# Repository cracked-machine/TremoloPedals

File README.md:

# TremoloPedals

[Atomizer Tremolo](atomizer/atomizer.md)

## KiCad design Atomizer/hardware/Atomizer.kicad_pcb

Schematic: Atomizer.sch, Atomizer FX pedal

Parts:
C1: 1uF; C_0805_2012Metric_Pad1.15x1.40mm_HandSolder
CP_INV1, CP_INV2: 10uF; CP_Elec_4x5.4; MouserNo 140-VE100M1CTR0405
C_BP3, C_BP4, C_BP5: 100nF; C_0805_2012Metric_Pad1.15x1.40mm_HandSolder; MouserNo 710-885012207098
J_IN1: JACK__MONO_2P_NC; 6_35MM_JACK_MONO_FlatTop_notab; MouserNo 550-10284G
J_OUT1: JACK__MONO_2P_NC; 6_35MM_JACK_MONO_FlatTop_notab; MouserNo 550-10284G
J_PWR1: Jack-DC; BarrelJack_Horizontal; MouserNo 502-RAPC722X
P_DEPTH1: B50k; Potentiometer_Alps_RK09L_Single_Vertical; MouserNo 688-RK09L1140A5P
P_VOL1: B10K; Potentiometer_Alps_RK09L_Single_Vertical; MouserNo 688-RK09L1140A66
R1, R3: 1K; R_0805_2012Metric_Pad1.15x1.40mm_HandSolder; MouserNo 279-CRGP0805F1K0
R2: 330R; R_0805_2012Metric_Pad1.15x1.40mm_HandSolder; MouserNo 71-CRCW0805330RFKEAC
R4: 270R; R_0805_2012Metric_Pad1.15x1.40mm_HandSolder; MouserNo 667-ERJ-6ENF2700V
R5: 47R; R_0805_2012Metric_Pad1.15x1.40mm_HandSolder; MouserNo 667-ERJ-6ENF47R0V
R6: 100K; R_0805_2012Metric_Pad1.15x1.40mm_HandSolder
R_GAIN1: 2K7; R_0805_2012Metric_Pad1.15x1.40mm_HandSolder; MouserNo 279-CRGCQ0805F2K7
R_PD1: 1M; R_0805_2012Metric_Pad1.15x1.40mm_HandSolder; MouserNo 755-UCR10EVHFSR022
U_BUF1: TL072; SOIC-8_3.9x4.9mm_P1.27mm; MouserNo 621-TL072SG-13
U_INV1: TC7662Bx0A; SOIC-8_3.9x4.9mm_P1.27mm; MouserNo 579-TC7660SEOA713
U_NREG1: LM337_SOT223; SOT-223-3_TabPin2; MouserNo 926-LM337IMP/NOPB
U_PREG1: LM317_3PinPackage; SOT-223-3_TabPin2; MouserNo 595-LM317DCYR

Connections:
+5V: C_BP3.2, R2.1, U_BUF1.8 (V+), U_PREG1.2; also elsewhere on the board
+9V: C_BP5.2, J_PWR1.2, U_INV1.1, U_INV1.8, U_PREG1.3
-5V: C_BP4.1, R4.2, U_BUF1.4 (V-), U_NREG1.3
-9V: CP_INV2.2, U_INV1.5, U_NREG1.2
/3PDT_2_EXT: J_IN1.1; also elsewhere on the board
/3PDT_3_EXT: R_PD1.1, U_BUF1.3 (+); also elsewhere on the board
/3PDT_5_EXT: J_OUT1.1; also elsewhere on the board
/3PDT_6_EXT: C1.1, R6.1; also elsewhere on the board
/Atomizer_Clock/CLK_OUT: P_DEPTH1.3; also elsewhere on the board
/GND: CP_INV2.1, C_BP3.1, C_BP4.2, C_BP5.1, J_IN1.2, J_IN1.3, J_IN1.4, J_OUT1.2, J_OUT1.3, J_OUT1.4, J_PWR1.1, R1.2, R3.2, R6.2, R_GAIN1.2, R_PD1.2, U_INV1.3, U_INV1.6; also elsewhere on the board
unnamed: C1.2, P_VOL1.3, U_BUF1.7
unnamed: CP_INV1.1, U_INV1.2
unnamed: CP_INV1.2, U_INV1.4
unnamed: P_DEPTH1.1, U_BUF1.1, U_BUF1.2 (-)
unnamed: P_DEPTH1.2, U_BUF1.5 (+)
unnamed: P_VOL1.1, P_VOL1.2, R_GAIN1.1, U_BUF1.6 (-)
unnamed: R1.1, R2.2, U_PREG1.1
unnamed: R3.1, R5.2, U_NREG1.1
unnamed: R4.1, R5.1

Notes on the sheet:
POWER SUPPLY
FOOTSWITCH
LFO
Guitar Fx pedals are Centre-Negative

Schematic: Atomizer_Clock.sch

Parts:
CP_FAST1: 22uF; CP_Elec_4x5.4; Tolerance 20%; Voltage Rating DC 10 DC; MouserNo 710-875105240003
CP_SLOW1: 220uF; CP_Elec_6.3x5.4; Voltage Rating DC 16 VDC; Tolerance 20 %; MouserNo 667-EEE-FPC221XAP
C_BP1: 100nF; C_0805_2012Metric_Pad1.15x1.40mm_HandSolder; MouserNo 710-885012207098
C_BP2: 10uF; C_0805_2012Metric_Pad1.15x1.40mm_HandSolder; MouserNo 81-GRM21BC81C106KE5K
D_HI1, D_HI2, D_HI3: 1N914_VF1; D_SOD-123; MouserNo 821-1N914BWRH
D_LED1: LED; LED_D5.0mm; MouserNo 859-LTL-307EE
D_LEDHI1: LED; LED_D3.0mm; MouserNo 941-C4SMABGFCR2T3451
D_LEDLO1: LED; LED_D3.0mm; MouserNo 941-C4SMABGFCR2T3451
D_LO1, D_LO2, D_LO3: 1N914_VF1; D_SOD-123; MouserNo 821-1N914BWRH
J_ICSP1: Conn_02x03_Odd_Even; PinHeader_2x03_P2.54mm_Vertical; MouserNo 538-22-28-4062
P_OSCOFF1: B10K; Potentiometer_Alps_RK09L_Single_Vertical; MouserNo 688-RK09L1140A66
P_OSCON1: B10K; Potentiometer_Alps_RK09L_Single_Vertical; MouserNo 688-RK09L1140A66
R_LPF1: 1K; R_0805_2012Metric_Pad1.15x1.40mm_HandSolder; MouserNo 279-CRGP0805F1K0
R_MLED1: 22K; R_0805_2012Metric_Pad1.15x1.40mm_HandSolder; MouserNo 667-ERJ-6ENF2202V
R_MODE1: 1K; R_0805_2012Metric_Pad1.15x1.40mm_HandSolder; MouserNo 279-CRGP0805F1K0
R_OSCOFF1: 1K; R_0805_2012Metric_Pad1.15x1.40mm_HandSolder; MouserNo 279-CRGP0805F1K0
R_OSCON1: 1K; R_0805_2012Metric_Pad1.15x1.40mm_HandSolder; MouserNo 279-CRGP0805F1K0
SW_ATTACK1: SW_SPDT; Dailywell_SPDT; MouserNo 108-2MS1T1B1M2QE-EVX
SW_MODE1: 1-1825910-4; SW_2-1825910-7; MouserNo 506-1-1825910-4
U_CLK1: ATtiny85-20SU; SOIJ-8_5.3x5.3mm_P1.27mm; MouserNo 556-ATTINY85-20SU
U_OPTO1: ACPL-217; SO-4_4.4x2.3mm_P1.27mm; MouserNo 630-ACPL-217-50BE

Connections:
/3PDT_8_EXT: C_BP1.1, C_BP2.1, D_LO3.2, J_ICSP1.2, R_OSCOFF1.2, R_OSCON1.2, U_CLK1.8 (VCC); also elsewhere on the board
/Atomizer_Clock/CLK_OUT: U_OPTO1.4; also elsewhere on the board
/Atomizer_Clock/CLK_OUT_PIN: J_ICSP1.1, R_LPF1.2, U_CLK1.6 (PB1)
/Atomizer_Clock/FREQ_ADJ_OFF_PIN: P_OSCOFF1.2, U_CLK1.3 (XTAL2/PB4)
/Atomizer_Clock/FREQ_ADJ_ON_PIN: P_OSCON1.2, U_CLK1.2 (XTAL1/PB3)
/Atomizer_Clock/MODE_BTN_PIN: J_ICSP1.4, R_MODE1.1, U_CLK1.5 (AREF/PB0)
/Atomizer_Clock/MODE_LED_PIN: J_ICSP1.3, R_MLED1.2, U_CLK1.7 (PB2)
/Atomizer_Clock/RESET: J_ICSP1.5, U_CLK1.1 (~RESET~/PB5)
/GND: CP_FAST1.2, CP_SLOW1.2, C_BP1.2, C_BP2.2, D_HI3.1, J_ICSP1.6, P_OSCOFF1.1, P_OSCON1.1, SW_MODE1.3, U_CLK1.4 (GND), U_OPTO1.2, U_OPTO1.3; also elsewhere on the board
unnamed: CP_FAST1.1, SW_ATTACK1.1
unnamed: CP_SLOW1.1, SW_ATTACK1.3
unnamed: D_HI1.1, D_HI2.2
unnamed: D_HI1.2, D_LEDHI1.1
unnamed: D_HI2.1, D_HI3.2
unnamed: D_LED1.1, SW_ATTACK1.2, U_OPTO1.1
unnamed: D_LED1.2, R_LPF1.1
unnamed: D_LEDHI1.2, D_LEDLO1.1, R_MLED1.1
unnamed: D_LEDLO1.2, D_LO1.1
unnamed: D_LO1.2, D_LO2.1
unnamed: D_LO2.2, D_LO3.1
unnamed: P_OSCOFF1.3, R_OSCOFF1.1
unnamed: P_OSCON1.3, R_OSCON1.1
unnamed: R_MODE1.2, SW_MODE1.2

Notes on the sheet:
Diodes prevent switch on when MODE_LED_PIN is in Tri-State
MOSI
VCC
GND
SCK
MISO
RESET

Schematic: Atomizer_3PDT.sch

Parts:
J_AUXTOMAIN1: Conn_02x05_Counter_Clockwise; IDCHeader_02x05_P2.54mm_Vertical_Counter_Clockwise; MouserNo 538-22-28-4102
J_MAINTOAUX1: Conn_02x05_Counter_Clockwise; IDCHeader_02x05_P2.54mm_Vertical_Clockwise; MouserNo 538-22-28-4102
SW_EN1: SW_3PDT_on_on; SW_3PDT_W18MM_L17.3MM_P5.3MM_D2MM; MouserNo 612-FS573PLT2B2M2QE

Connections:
+5V: J_MAINTOAUX1.9; also elsewhere on the board
/3PDT_2_EXT: J_MAINTOAUX1.2; also elsewhere on the board
/3PDT_3_EXT: J_MAINTOAUX1.3; also elsewhere on the board
/3PDT_4_EXT: J_MAINTOAUX1.1, J_MAINTOAUX1.4
/3PDT_5_EXT: J_MAINTOAUX1.5; also elsewhere on the board
/3PDT_6_EXT: J_MAINTOAUX1.6; also elsewhere on the board
/3PDT_8_EXT: J_MAINTOAUX1.8; also elsewhere on the board
/Atomizer_3PDT/3PDT_1_INT: J_AUXTOMAIN1.1, SW_EN1.1
/Atomizer_3PDT/3PDT_2_INT: J_AUXTOMAIN1.2, SW_EN1.2
/Atomizer_3PDT/3PDT_3_INT: J_AUXTOMAIN1.3, SW_EN1.3
/Atomizer_3PDT/3PDT_4_INT: J_AUXTOMAIN1.4, SW_EN1.4
/Atomizer_3PDT/3PDT_5_INT: J_AUXTOMAIN1.5, SW_EN1.5
/Atomizer_3PDT/3PDT_6_INT: J_AUXTOMAIN1.6, SW_EN1.6
/Atomizer_3PDT/3PDT_7_INT: J_AUXTOMAIN1.7, SW_EN1.7
/Atomizer_3PDT/3PDT_8_INT: J_AUXTOMAIN1.8, SW_EN1.8
/Atomizer_3PDT/3PDT_9_INT: J_AUXTOMAIN1.9, SW_EN1.9

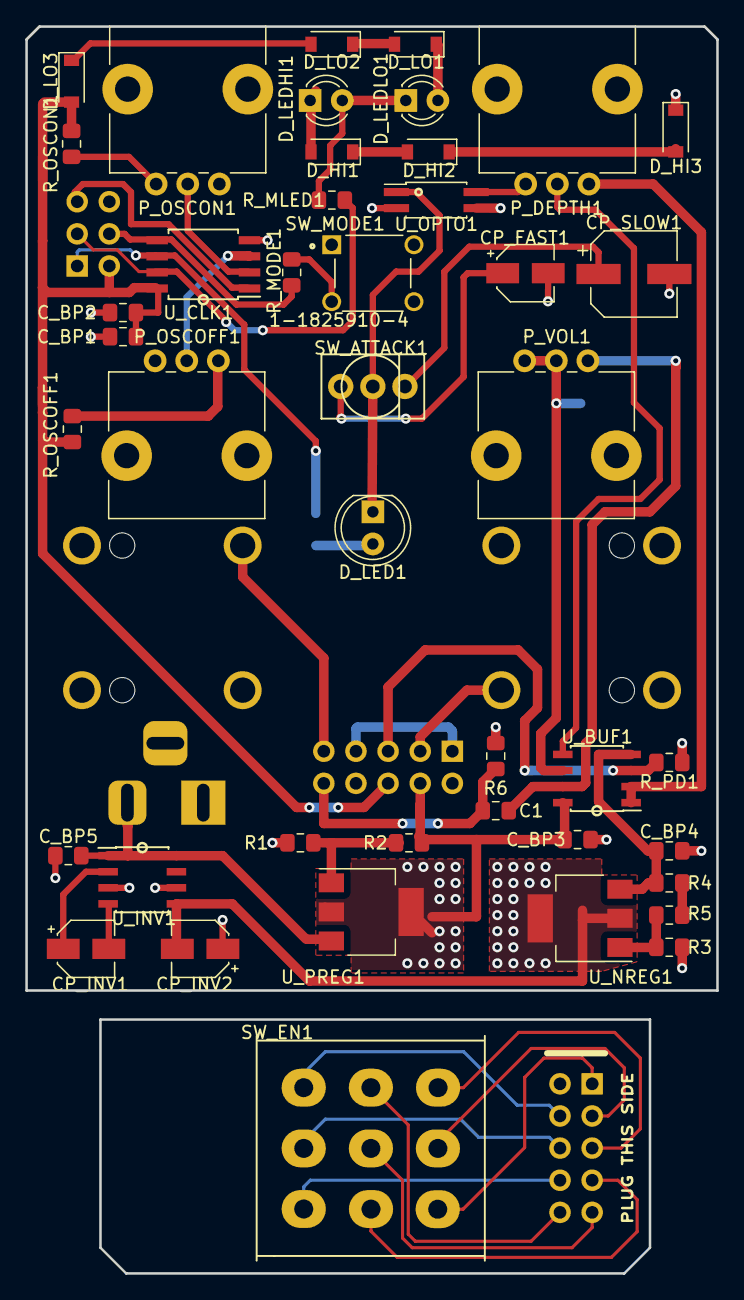
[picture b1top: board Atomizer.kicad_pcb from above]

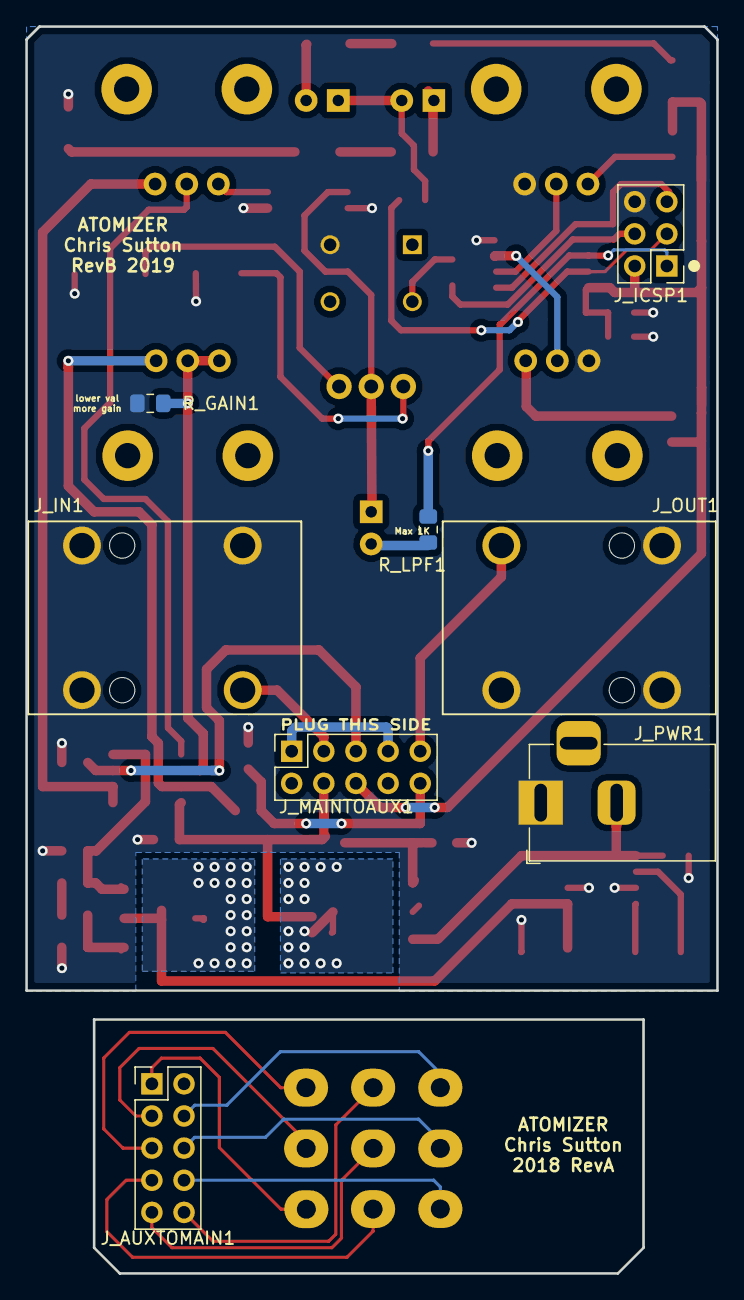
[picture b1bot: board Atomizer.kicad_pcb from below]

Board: 2 copper layers, 54.6 x 98.6 mm, 51 parts (8 on the bottom side), 50 nets.

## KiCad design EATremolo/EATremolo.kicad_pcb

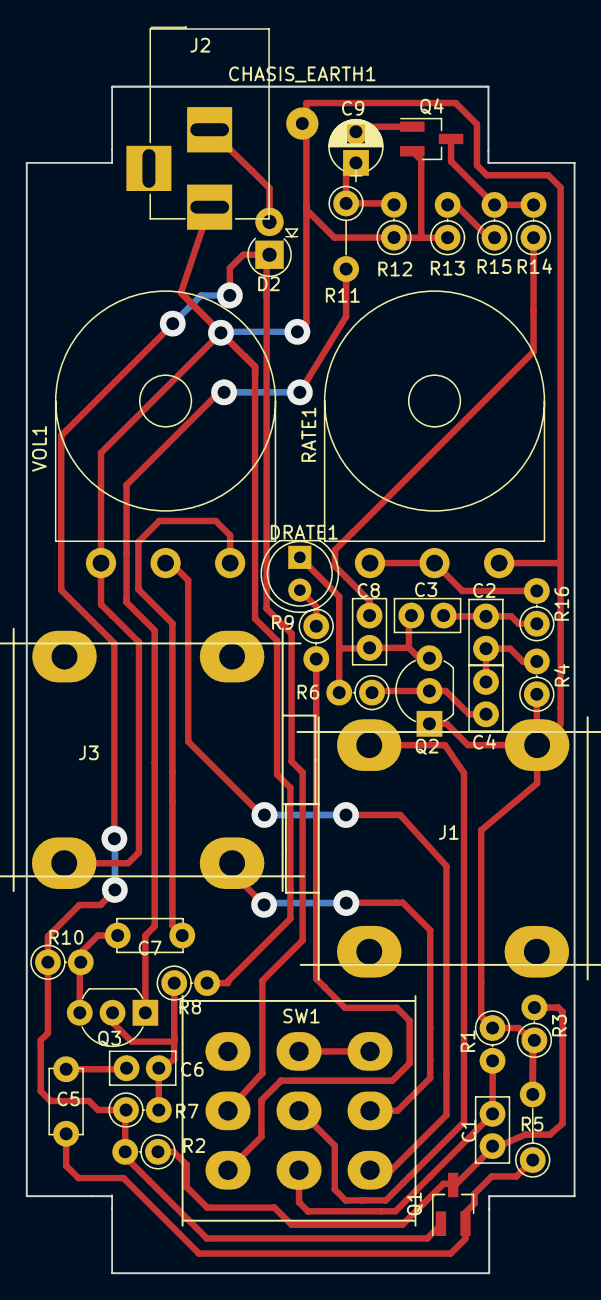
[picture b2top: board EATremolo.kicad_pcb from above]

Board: 2 copper layers, 42.4 x 96.5 mm, 38 parts (0 on the bottom side), 27 nets.

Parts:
C1: 47nF; C_Disc_2mmPads
C2, C3, C4: 1uF; C_Disc_2mmPads
C5: 10uF; C_Disc_P5.0mm_2mmPads
C6: 220nF; C_Disc_2mmPads
C7: 470nF; C_Disc_P5.0mm_2mmPads
C8: 470nF; C_Disc_2mmPads
C9: 10uF; CP_Radial_D4_P2_PadSize2_Drill1
CHASIS_EARTH1: CONN_01X01; SolderWirePad_single_1mmDrill
D2: D_Schottky; D_DO-41_SOD81_P2.54mm_Vertical_AnodeUp
DRATE1: LED; LED_D5.0mm
J1, J3: JACK__MONO_2P_NC; JackSocket_Mono_PCB
J2: BARREL_JACK
Q1, Q4: Q_NJFET_DSG; SOT-23_Handsoldering
Q2, Q3: Q_NPN_EBC; TO-92_Inline_Wide
R1, R2, R3: 1M; R_Axial_DIN0207_Vertical_2mmPad
R4: 15K; R_Axial_DIN0207_Vertical_2mmPad
R5: 10K; R_Axial_DIN0207_P5.08mm_2mmPads
R6: 2.2M; R_Axial_DIN0207_Vertical_2mmPad
R7: 560K; R_Axial_DIN0207_Vertical_2mmPad
R8: 150K; R_Axial_DIN0207_Vertical_2mmPad
R9: 10K; R_Axial_DIN0207_Vertical_2mmPad
R10: 4.7K; R_Axial_DIN0207_Vertical_2mmPad
R11: 180R; R_Axial_DIN0207_P5.08mm_2mmPads
R12: 1.2K; R_Axial_DIN0207_Vertical_2mmPad
R13: 68k; R_Axial_DIN0207_Vertical_2mmPad
R14: 180K; R_Axial_DIN0207_Vertical_2mmPad
R15: 100K; R_Axial_DIN0207_Vertical_2mmPad
R16: 1K; R_Axial_DIN0207_Vertical_2mmPad
RATE1: B100K; Potentiometer_Omeg_PC16PU_Horizontal
SW1: SW_3PDT_on_on; SW_3PDT_W18MM_L17.3MM_P5.3MM_D2MM
VOL1: A25K; Potentiometer_Omeg_PC16PU_Horizontal

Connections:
/+9V: D2.1, Q1.1, R2.2, R7.1, R10.1, SW1.2
/GND: CHASIS_EARTH1.1, J1.4, J2.1, J3.4, Q2.1, Q4.2, R1.1, R3.1, R4.1, R5.2, R8.2, R12.1, R13.1, RATE1.1, VOL1.3
unnamed: C1.1, Q1.3, R2.1, R3.2
unnamed: C1.2, R1.2, SW1.6
unnamed: C2.1, C3.2, R16.1
unnamed: C2.2, C4.1, R4.2
unnamed: C3.1, C8.2, DRATE1.1, Q2.3, R6.2
unnamed: C4.2, Q2.2, R6.1
unnamed: C5.1, Q1.2, R5.1
unnamed: C5.2, C6.2
unnamed: C6.1, Q3.2, R7.2, R8.1
unnamed: C7.1, VOL1.1
unnamed: C7.2, Q3.3, R10.2
unnamed: C8.1, R14.1
unnamed: C9.1, R11.1, R12.2
unnamed: C9.2, Q4.1
unnamed: D2.2, J2.2
unnamed: DRATE1.2, R9.1
unnamed: J1.1, SW1.5
unnamed: J3.1, SW1.8
unnamed: Q3.1, R11.2
unnamed: Q4.3, R14.2, R15.2
unnamed: R9.2, SW1.3
unnamed: R13.2, R15.1
unnamed: R16.2, RATE1.2, RATE1.3
unnamed: SW1.4, SW1.7
unnamed: SW1.9, VOL1.2

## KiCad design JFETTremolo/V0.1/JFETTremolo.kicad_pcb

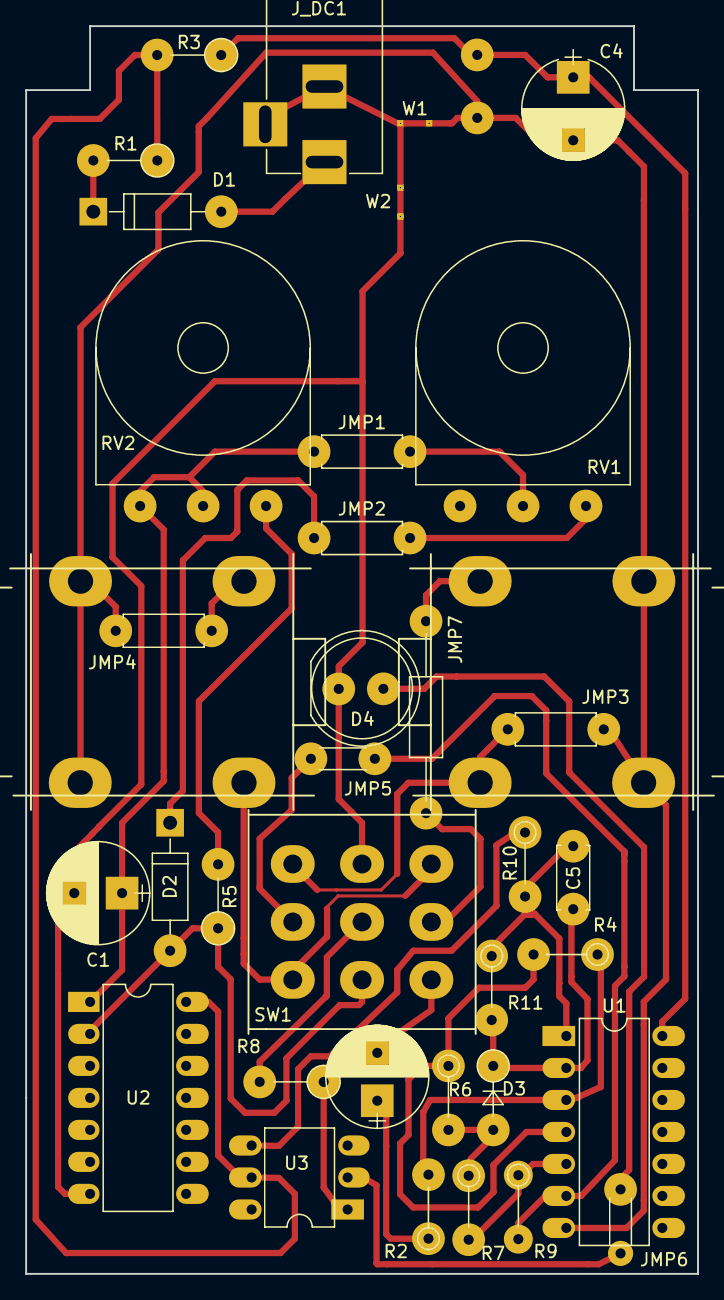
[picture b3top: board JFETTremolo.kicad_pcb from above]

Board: 2 copper layers, 53.3 x 99.1 mm, 38 parts (1 on the bottom side), 31 nets.

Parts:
C1: 10U; CP_Radial_D8.0mm_P3.80mm
C2: 1u; CP_Radial_D8.0mm_P3.80mm
C3: 10n; C_Disc_D5.0mm_W2.5mm_P5.00mm
C4: 47u; CP_Radial_D8.0mm_P5.00mm
C5: 470n; C_Disc_D5.0mm_W2.5mm_P5.00mm
D1, D2: D; D_DO-41_SOD81_P10.16mm_Horizontal
D3: D; D_DO-35_SOD27_P5.08mm_Vertical_AnodeUp
D4: LED; LED_D8.0mm
JMP1, JMP2, JMP3, JMP4: 0; R_Axial_DIN0207_L6.3mm_D2.5mm_P7.62mm_Horizontal
JMP5, JMP6: 0; R_Axial_DIN0204_L3.6mm_D1.6mm_P5.08mm_Horizontal
JMP7: 0; R_Axial_DIN0207_L6.3mm_D2.5mm_P15.24mm_Horizontal
J_DC1: BARREL_JACK
J_IN1: JACK__MONO_2P_NC; JackSocket_Mono_PCB
J_OUT1: JACK__MONO_2P_NC; JackSocket_Mono_PCB
R1: 100R; R_Axial_DIN0207_L6.3mm_D2.5mm_P5.08mm_Vertical
R2, R4, R6, R7, R9, R10, R11: 100K; R_Axial_DIN0204_L3.6mm_D1.6mm_P5.08mm_Vertical
R3, R5: 10K; R_Axial_DIN0207_L6.3mm_D2.5mm_P5.08mm_Vertical
R8: 100K; R_Axial_DIN0207_L6.3mm_D2.5mm_P5.08mm_Vertical
RV1, RV2: 100K; Potentiometer_Omeg_PC16PU_Horizontal
SW1: SW_3PDT_on_on; SW_3PDT_W18MM_L17.3MM_P5.3MM_D2MM
U1: CD4069; DIP-14_W7.62mm
U2: 4584; DIP-14_W7.62mm
U3: 4N25; DIP-6_W7.62mm
W1, W2: NetTie

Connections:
/clk_gnd: C1.2, D4.1, SW1.6, U2.7, W2.2
/clk_ota: D2.2, R5.1, SW1.4, U2.2
/clk_vdd: R1.1, R3.2, U2.14, U3.5
/fxin: C2.2, SW1.1
/fxout: JMP5.1, JMP5.2, R9.2, SW1.8, U1.6
/gnd: J_DC1.2, J_DC1.3, W1.1, W2.1
/mclk: C5.1, D3.1, R11.2, U1.2
/ota_clk: R10.1, U3.4
/sig_gnd: C3.2, C4.2, JMP3.1, JMP3.2, JMP4.2, J_IN1.2, J_IN1.3, J_IN1.4, J_OUT1.3, J_OUT1.4, SW1.9, U1.7, W1.2
/sig_out: J_OUT1.1, SW1.3, SW1.7
/sig_vdd: C3.1, C4.1, R3.1, U1.14
/sigin: JMP7.2, J_IN1.1
unnamed: C1.1, JMP1.1, RV2.2, RV2.3, U2.1
unnamed: C2.1, R2.1
unnamed: C5.2, R10.2, R11.1, U1.1
unnamed: D1.1, R1.2
unnamed: D1.2, J_DC1.1
unnamed: D2.1, JMP2.1
unnamed: D3.2, R6.2, R7.1
unnamed: D4.2, JMP6.2
unnamed: JMP1.2, RV1.2
unnamed: JMP2.2, RV1.1
unnamed: JMP4.1, J_OUT1.2
unnamed: JMP6.1, U3.2
unnamed: JMP7.1, SW1.2
unnamed: R2.2, R4.1, U1.3
unnamed: R4.2, R6.1, U1.4
unnamed: R5.2, RV2.1
unnamed: R7.2, R9.1, U1.5
unnamed: R8.1, U3.1
unnamed: R8.2, SW1.5

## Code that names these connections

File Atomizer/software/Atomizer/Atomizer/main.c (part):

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volatile unsigned int lowerpot = 0;		// the bottom potentiometer

#define _ADCLA 0x20	// ADC Left Adjust Result
#define _ADC0EN 0x00	// PB5 - MUX(3:0) = 0000; Use bitwise AND to set ADC0 ( e.g. ADMUX &= ADC0EN; )
#define _ADC1EN 0x01	// PB2 - MUX(3:0) = 0001; Use bitwise OR to set ADC1 ( e.g. ADMUX |= ADC1EN; )
#define _ADC2EN 0x02	// PB4 - MUX(3:0) = 0010; Use bitwise OR to set ADC2 ( e.g. ADMUX |= ADC2EN; )
#define _ADC3EN 0x03	// PB3 - MUX(3:0) = 0011; Use bitwise OR to set ADC3 ( e.g. ADMUX |= ADC3EN; )

// PCINT variables
// NORMAL	=	Synchronized-duty Tremolo (lowerpot does nothing)
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	/////	PIN USAGE
	///////////////////////
	///
	//		PB0 - INPUT  - Mode Button
	//		PB1 - OUTPUT - Tremolo Clock 
	//		PB2 - OUTPUT - Mode LEDs
	//		PB3 - INPUT  - Hi Adjust Pot
	//		PB4 - INPUT  - Lo Adjust Pot
	///
	////////////////////////
	
	
	
	// clock signal (output)
	PORTB |= (1<<PB1);
	DDRB |= (1<<DDB1);
	
	// ADC3+4 (input)
	PORTB &= ~(1<<PB3);
	DDRB &= ~(1<<DDB3);
	PORTB &= ~(1<<PB4);
	DDRB &= ~(1<<DDB4);
		
	///////////////////////////////////
	//// PCINT setup
	///////////////////////////////////
	
	// set PB0 to input
	DDRB &= ~(1<<DDB0);
	// set PB0 pull-up
	PORTB |= 1<<PB0;
	
	// enable PC Interrupts
	GIMSK |= (1<<PCIE);
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	///////////////////////////////////

	
	// VCC used as Voltage Reference, disconnected from PB0 (AREF).
	ADMUX &= ~((1<<REFS0) | (1<<REFS1));
	
	// ADC Right Adjust Result
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		case NORMAL:
			// Tri-State mode LED pin (LEDS off)
			DDRB &= ~(1<<DDB2);
			PORTB &= ~(1<<PB2);
			break;
			
		case SKEW:
			// Logic one to mode LED pin 
			DDRB |= (1<<DDB2);
			PORTB |= (1<<PB2);
			break;
		
		case SWEEP:
			// Logic zero to mode LED pin 
			DDRB |= (1<<DDB2);
			PORTB &= ~(1<<PB2);
			break;
		/* abandoned *see top*
		case FADE:
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	{
		case NORMAL:
			
			// disable Timer0 output to OC0B (PB1)
			TCCR0A = 0;
			
			///////////////////////////////////
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			// Timer/Counter1 is reset to $00 after a compare match with OCR1C register value 
			TCCR1 |= (1<<CTC1);
	
			// enable toggle output on OC1A (PB1) output line.
			TCCR1 |= (0<<COM1A1) | (1<<COM1A0);
			
			// Timer/Counter1 Prescale Select PCK/2048
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			
		case SKEW:
			
			// disable Timer1 output to OC1A (PB1)
			TCCR1 = 0;
			
			///////////////////////////////////
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			
			//Normal port operation, OC0A disconnected
			TCCR0A |= (0<<COM0A1) | (0<<COM0A0);
			// Enable OC0B (PB1) output. (Clear OC0B on Compare Match, set OC0B at BOTTOM - non-inverting mode)
			TCCR0A |= (1<<COM0B1) | (0<<COM0B0);
			// Mode 5: phase PWM
			TCCR0A |= (0<<WGM01) | (1<<WGM00);
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		
		case SWEEP:
		
			// disable Timer0 output to OC0B (PB1)
			TCCR0A = 0;
			
			///////////////////////////////////
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			// Timer/Counter1 is reset to $00 after a compare match with OCR1C register value
			TCCR1 |= (1<<CTC1);
			
			// enable toggle output on OC1A (PB1) output line.
			TCCR1 |= (0<<COM1A1) | (1<<COM1A0);
			
			// Timer/Counter1 Prescale Select PCK/2048
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			/*  abandoned *see top*
			case FADE:
			
			// disable Timer1 output to OC1A (PB1)
			TCCR1 = 0;
			
			///////////////////////////////////
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			
			//Normal port operation, OC0A disconnected
			TCCR0A |= (0<<COM0A1) | (0<<COM0A0);
			// Enable OC0B (PB1) output. (Clear OC0B on Compare Match, set OC0B at BOTTOM - non-inverting mode)
			TCCR0A |= (1<<COM0B1) | (0<<COM0B0);
			// Mode 5: phase PWM
			TCCR0A |= (0<<WGM01) | (1<<WGM00);
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
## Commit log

2017-12-01 EATemolo BOM update
2017-12-02 EA Tremolo Layout completed
2017-12-02 saved EATremolo
2017-12-04 EA Tremolo Rev2
2017-12-10 Created EATremoloSMD
2017-12-12 board outline update
2017-12-12 Updated EATremoloSMD
2017-12-13 EAMTremoloSMD update
    pcb header alignment
2017-12-13 Board Description Updates
2017-12-15 BoardUpdate
2018-01-20 Added 555TremoloSMD
2018-11-06 Added HexTremolo
2018-11-07 UPDATED SCHEMATIC
    removed clk tick from audio path
    - current limiting resistors at osc vcc (1W)
    - LPF at FX-side of OPTOCOUPLER
2018-11-08 RevA
2018-11-09 Added 555PWMTremolo Schematic
2018-11-09 Completed 555PWMTremolo Layout RevA
2018-11-09 Tidied up 555 layout
2018-11-09 Final RevA
2018-11-14 Board Layout Corrections
    Aux Board Ribbon cable header inversed
2018-11-15 Added second 555 IC bypass cap
2018-11-15 Reorganised docs folder
2018-11-16 Corrected DC Jack polarity
2018-11-25 added Atomizer AVR Design
    added Atomizer AVR Design
2018-11-26 Added Atomizer Design and Code
2018-11-27 Added 3d Model
2018-11-27 updated firmware
    - removed random mode (sounds rubbish)
    - added sweep mode (sounds awesome)
2018-11-28 Finished Atomizer RevB
2018-11-29 Finished Atomizer RevA
2018-12-02 Updated BOM
2018-12-05 Added additional docs
2018-12-09 Updated Atomizer firmware
    Fixed pot range bugs
2018-12-28 atomizer schematic graphics update
2018-12-28 Updated BOM. Converted to Mouser list. Moved LED away from switch
2018-12-31 updated atomizer schema documentation
2019-01-14 fixed sweep mode bug
    During SWEEP mode (upperpot < 50) can cause MCU to reset. Fix is to set min value for upperpot when in this mode. Line 300 (TIMER1_COMPA_vect)
2019-01-14 Tested FADE mode; abandoned.
2019-01-14 save update
2019-04-14 updated firmware to EEPROM write/read last used mode
2019-04-14 autosave
2019-06-01 updated atomizer
    - changed input pulldown resistor from 22M to 1M
    - added output lpf filter (1uF, 100K)
    - updated docs
2019-07-11 added IBOM
2019-07-11 added master/docs/readme.md
2019-07-11 added atomizer_ibom.html
2019-07-11 Rename atomizer_ibom.html to index.html
2019-07-11 Rename index.html to atomizerbom.html
2019-07-11 Set theme jekyll-theme-hacker
